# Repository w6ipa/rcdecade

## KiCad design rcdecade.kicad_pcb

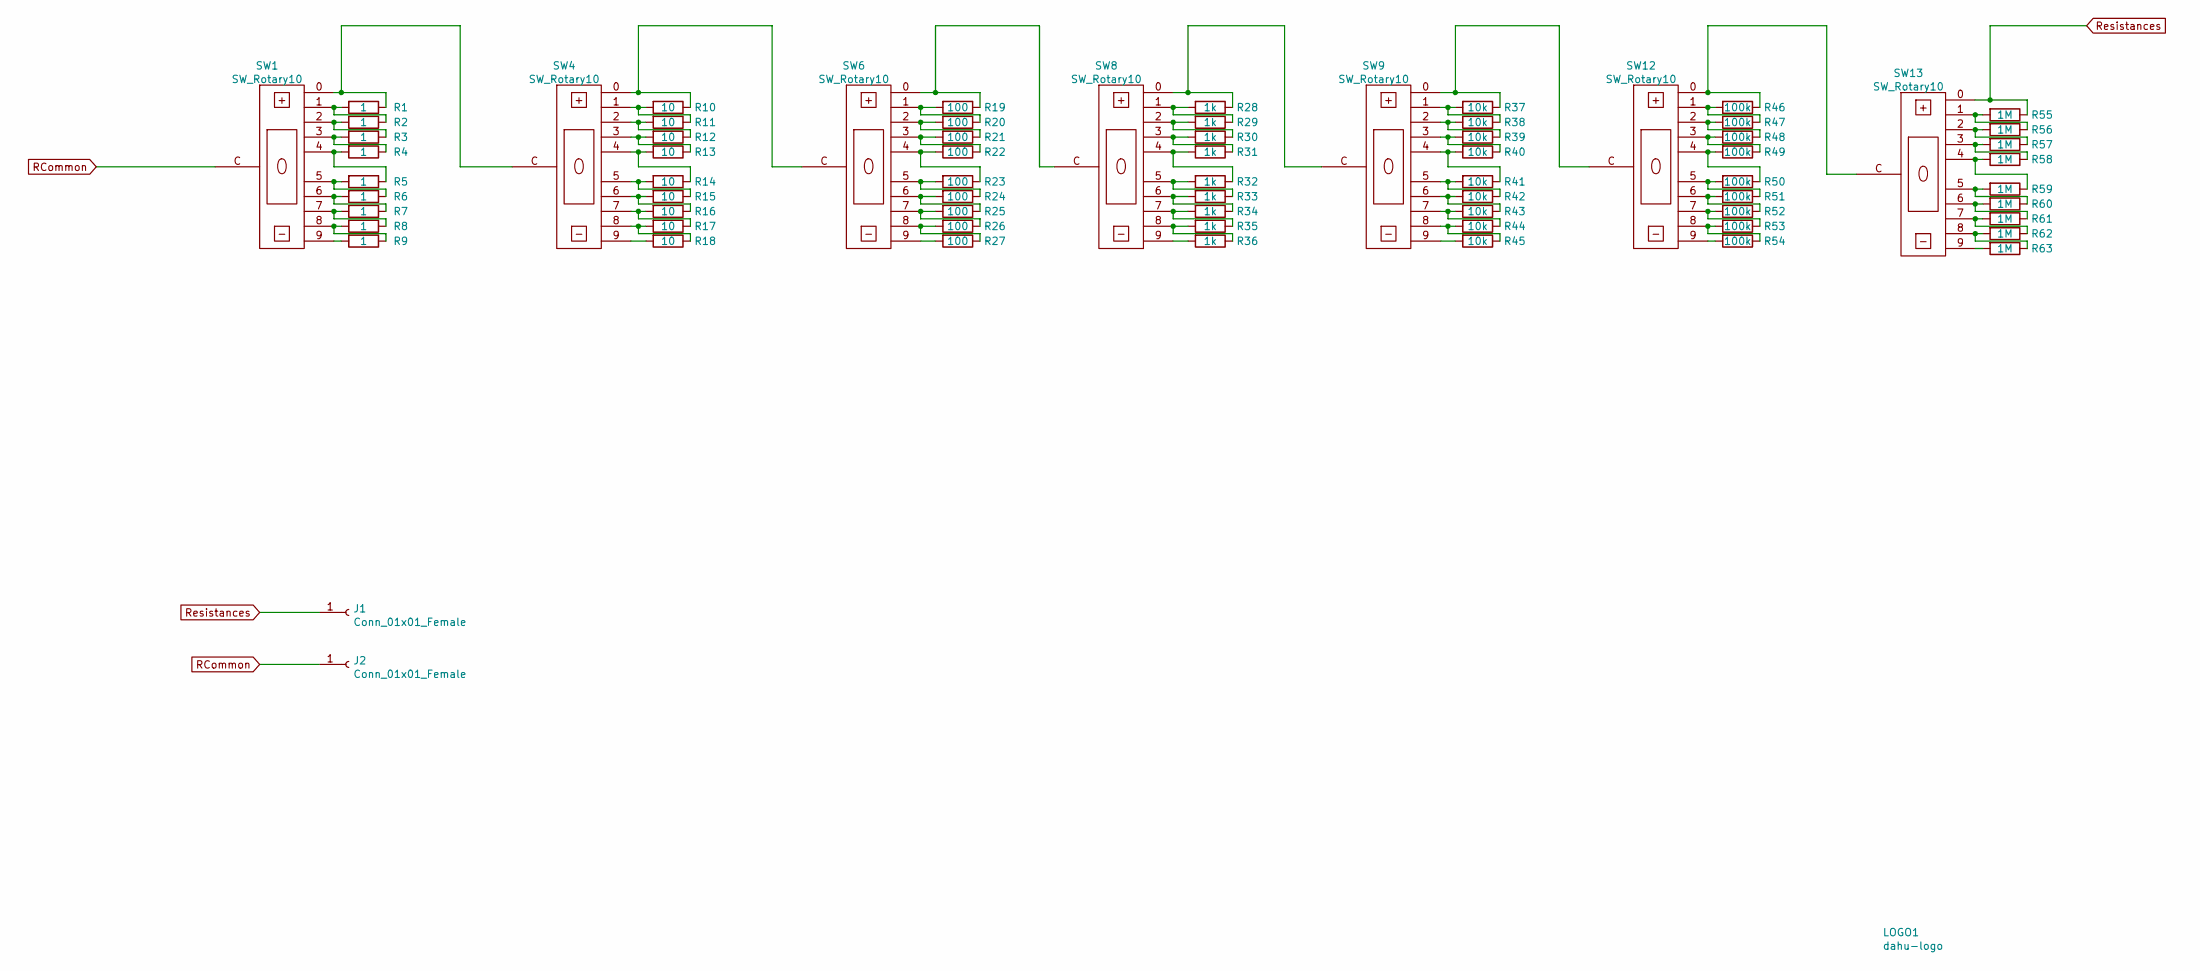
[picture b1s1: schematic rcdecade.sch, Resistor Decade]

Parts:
J1, J2: Conn_01x01_Female; SolderWirePad_1x01_Drill2mm
LOGO1: dahu-logo; W6IPA-Logo-9mmx8mm
R1, R2, R3, R4, R5, R6, R7, R8, R9: 1; R_1210_3225Metric
R10, R11, R12, R13, R14, R15, R16, R17, R18: 10; R_1210_3225Metric
R19, R20, R21, R22, R23, R24, R25, R26, R27: 100; R_1210_3225Metric
R28, R29, R30, R31, R32, R33, R34, R35, R36: 1k; R_1210_3225Metric
R37, R38, R39, R40, R41, R42, R43, R44, R45: 10k; R_1210_3225Metric
R46, R47, R48, R49, R50, R51, R52, R53, R54: 100k; R_1210_3225Metric
R55, R56, R57, R58, R59, R60, R61, R62, R63: 1M; R_1210_3225Metric
SW1, SW4, SW6, SW8, SW9, SW12, SW13: SW_Rotary10; Switch_Thumbwheel_Digital

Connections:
unnamed: R1.1, SW1.0 (1), SW4.C (11)
unnamed: R1.2, R2.1, SW1.1 (2)
unnamed: R2.2, R3.1, SW1.2 (3)
unnamed: R3.2, R4.1, SW1.3 (4)
unnamed: R4.2, R5.1, SW1.4 (5)
unnamed: R5.2, R6.1, SW1.5 (6)
unnamed: R6.2, R7.1, SW1.6 (7)
unnamed: R7.2, R8.1, SW1.7 (8)
unnamed: R8.2, R9.1, SW1.8 (9)
unnamed: R9.2, SW1.9 (10)
unnamed: R10.1, SW4.0 (1), SW6.C (11)
unnamed: R10.2, R11.1, SW4.1 (2)
unnamed: R11.2, R12.1, SW4.2 (3)
unnamed: R12.2, R13.1, SW4.3 (4)
unnamed: R13.2, R14.1, SW4.4 (5)
unnamed: R14.2, R15.1, SW4.5 (6)
unnamed: R15.2, R16.1, SW4.6 (7)
unnamed: R16.2, R17.1, SW4.7 (8)
unnamed: R17.2, R18.1, SW4.8 (9)
unnamed: R18.2, SW4.9 (10)
unnamed: R19.1, SW6.0 (1), SW8.C (11)
unnamed: R19.2, R20.1, SW6.1 (2)
unnamed: R20.2, R21.1, SW6.2 (3)
unnamed: R21.2, R22.1, SW6.3 (4)
unnamed: R22.2, R23.1, SW6.4 (5)
unnamed: R23.2, R24.1, SW6.5 (6)
unnamed: R24.2, R25.1, SW6.6 (7)
unnamed: R25.2, R26.1, SW6.7 (8)
unnamed: R26.2, R27.1, SW6.8 (9)
unnamed: R27.2, SW6.9 (10)
unnamed: R28.1, SW8.0 (1), SW9.C (11)
unnamed: R28.2, R29.1, SW8.1 (2)
unnamed: R29.2, R30.1, SW8.2 (3)
unnamed: R30.2, R31.1, SW8.3 (4)
unnamed: R31.2, R32.1, SW8.4 (5)
unnamed: R32.2, R33.1, SW8.5 (6)
unnamed: R33.2, R34.1, SW8.6 (7)
unnamed: R34.2, R35.1, SW8.7 (8)
unnamed: R35.2, R36.1, SW8.8 (9)
unnamed: R36.2, SW8.9 (10)
unnamed: R37.1, SW9.0 (1), SW12.C (11)
unnamed: R37.2, R38.1, SW9.1 (2)
unnamed: R38.2, R39.1, SW9.2 (3)
unnamed: R39.2, R40.1, SW9.3 (4)
unnamed: R40.2, R41.1, SW9.4 (5)
unnamed: R41.2, R42.1, SW9.5 (6)
unnamed: R42.2, R43.1, SW9.6 (7)
unnamed: R43.2, R44.1, SW9.7 (8)
unnamed: R44.2, R45.1, SW9.8 (9)
unnamed: R45.2, SW9.9 (10)
unnamed: R46.1, SW12.0 (1), SW13.C (11)
unnamed: R46.2, R47.1, SW12.1 (2)
unnamed: R47.2, R48.1, SW12.2 (3)
unnamed: R48.2, R49.1, SW12.3 (4)
unnamed: R49.2, R50.1, SW12.4 (5)
unnamed: R50.2, R51.1, SW12.5 (6)
unnamed: R51.2, R52.1, SW12.6 (7)
unnamed: R52.2, R53.1, SW12.7 (8)
unnamed: R53.2, R54.1, SW12.8 (9)
unnamed: R54.2, SW12.9 (10)
unnamed: R55.2, R56.1, SW13.1 (2)
unnamed: R56.2, R57.1, SW13.2 (3)
unnamed: R57.2, R58.1, SW13.3 (4)
unnamed: R58.2, R59.1, SW13.4 (5)
unnamed: R59.2, R60.1, SW13.5 (6)
unnamed: R60.2, R61.1, SW13.6 (7)
unnamed: R61.2, R62.1, SW13.7 (8)
unnamed: R62.2, R63.1, SW13.8 (9)
unnamed: R63.2, SW13.9 (10)
RCommon: J2.1, SW1.C (11)
Resistances: J1.1, R55.1, SW13.0 (1)

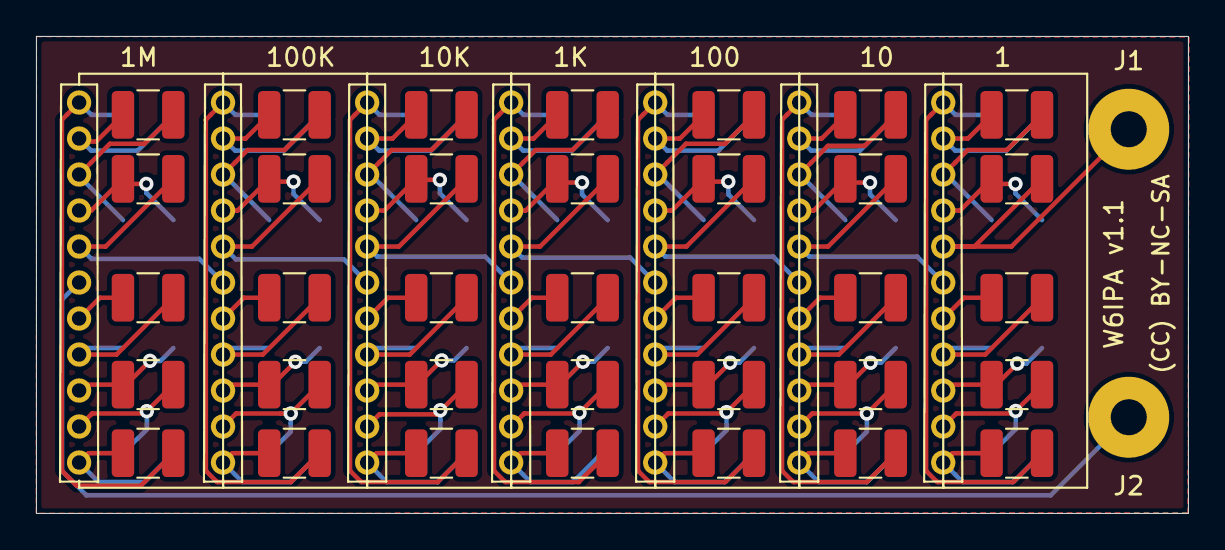
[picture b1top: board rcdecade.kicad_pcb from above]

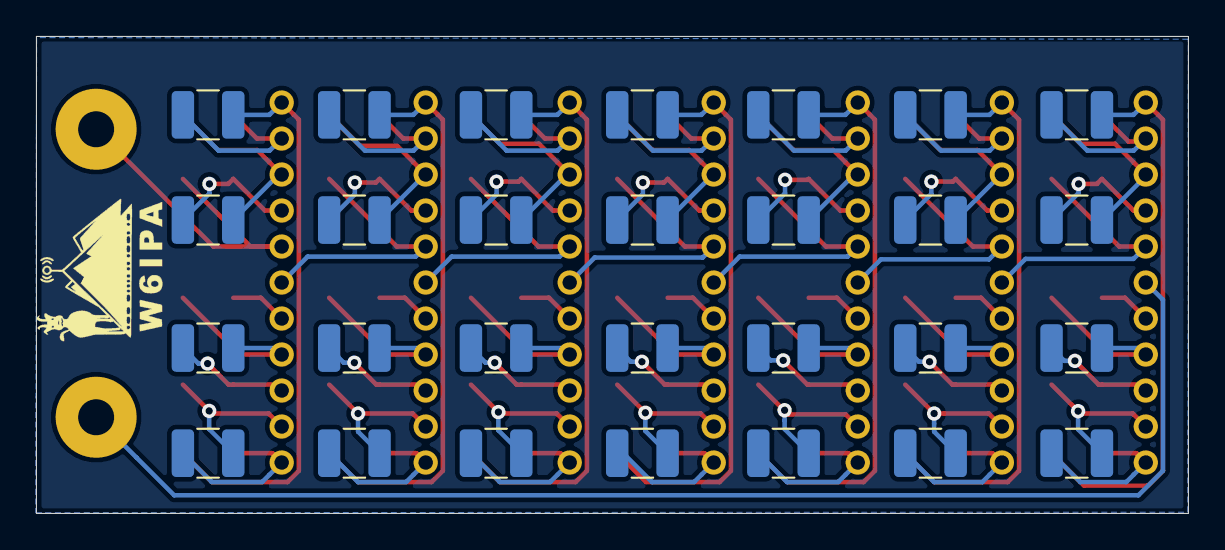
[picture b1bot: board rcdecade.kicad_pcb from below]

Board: 2 copper layers, 64.0 x 26.5 mm, 73 parts (29 on the bottom side), 71 nets.

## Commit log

2020-02-18 R Decade only
2020-02-26 Add missing trace in the x1
2020-03-01 Fix // serial
2020-03-03 disconnect copper - v1.1
